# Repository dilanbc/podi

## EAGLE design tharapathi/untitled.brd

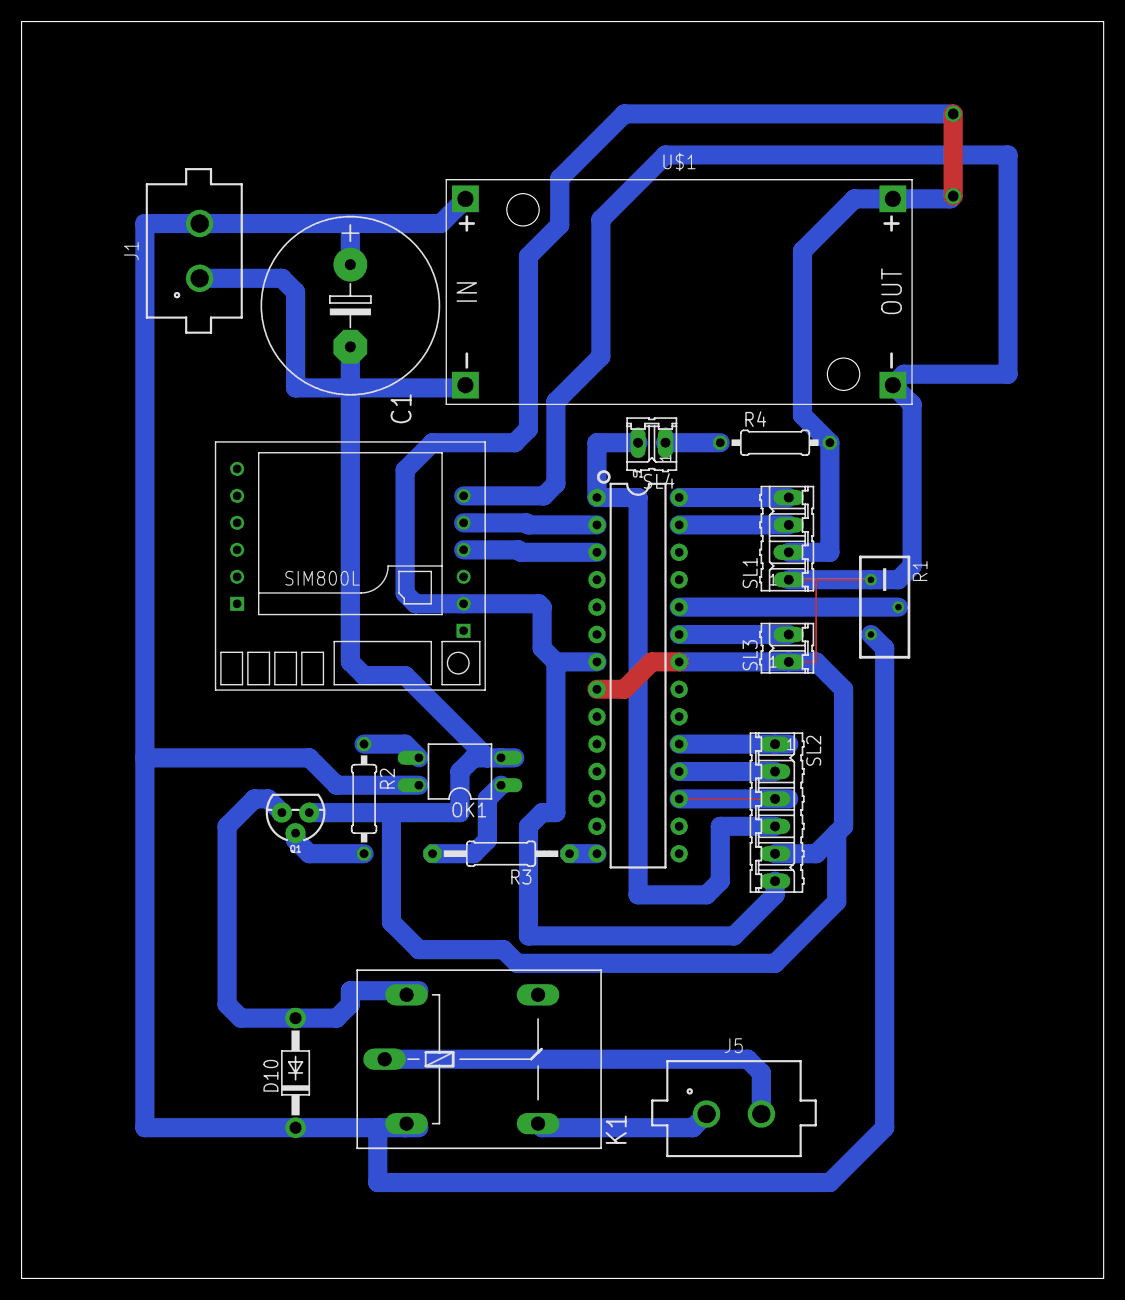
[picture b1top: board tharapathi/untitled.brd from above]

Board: 2 copper layers, 100.3 x 116.5 mm, 18 parts (0 on the bottom side), 21 nets.

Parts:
C1: E7,5-16
D10: 1N4004; DO41-10
J1, J5: 691305530002
K1: G5L; G5LE
OK1: PC817; DIL04
Q1: 200mA/40V; TO-92
R1: RTRIM3296Y
R2, R4: 0207/10
R3: 0207/12
SL1: 04P
SL2: 06P
SL3, SL4: 02P
U1: 328P; DIP28
U$1: DC-DC-STEP-DOWN-LM2596
U$2: SIM800LMODULE

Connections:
GND: C1.-, J1.1, OK1.2, Q1.1, R1.1, SL1.1, SL2.5, SL3.1, U1.8, U1.22, U$1.IN-, U$1.OUT-, U$2.GND
unnamed: OK1.1, R3.2
unnamed: R1.2, U1.24
unnamed: SL2.1, U1.19
unnamed: SL2.2, U1.18
unnamed: SL2.3, U1.17
unnamed: SL2.4, SL4.2, U1.1
unnamed: SL3.2, U1.23
unnamed: D10.A, K1.2, Q1.3
unnamed: J5.2, K1.P
unnamed: J5.1, K1.S
unnamed: Q1.2, R2.2
unnamed: OK1.3, R2.1
unnamed: R4.1, SL4.1
PWR: C1.+, D10.C, J1.2, K1.1, OK1.4, R1.3, U$1.IN+
RL: R3.1, U1.14
RX: U1.2, U$2.TX
SCL: SL1.4, U1.28
SDA: SL1.3, U1.27
TX: U1.3, U$2.RX
VCC: R4.2, SL1.2, SL2.6, U1.7, U$1.OUT+, U$2.VCC

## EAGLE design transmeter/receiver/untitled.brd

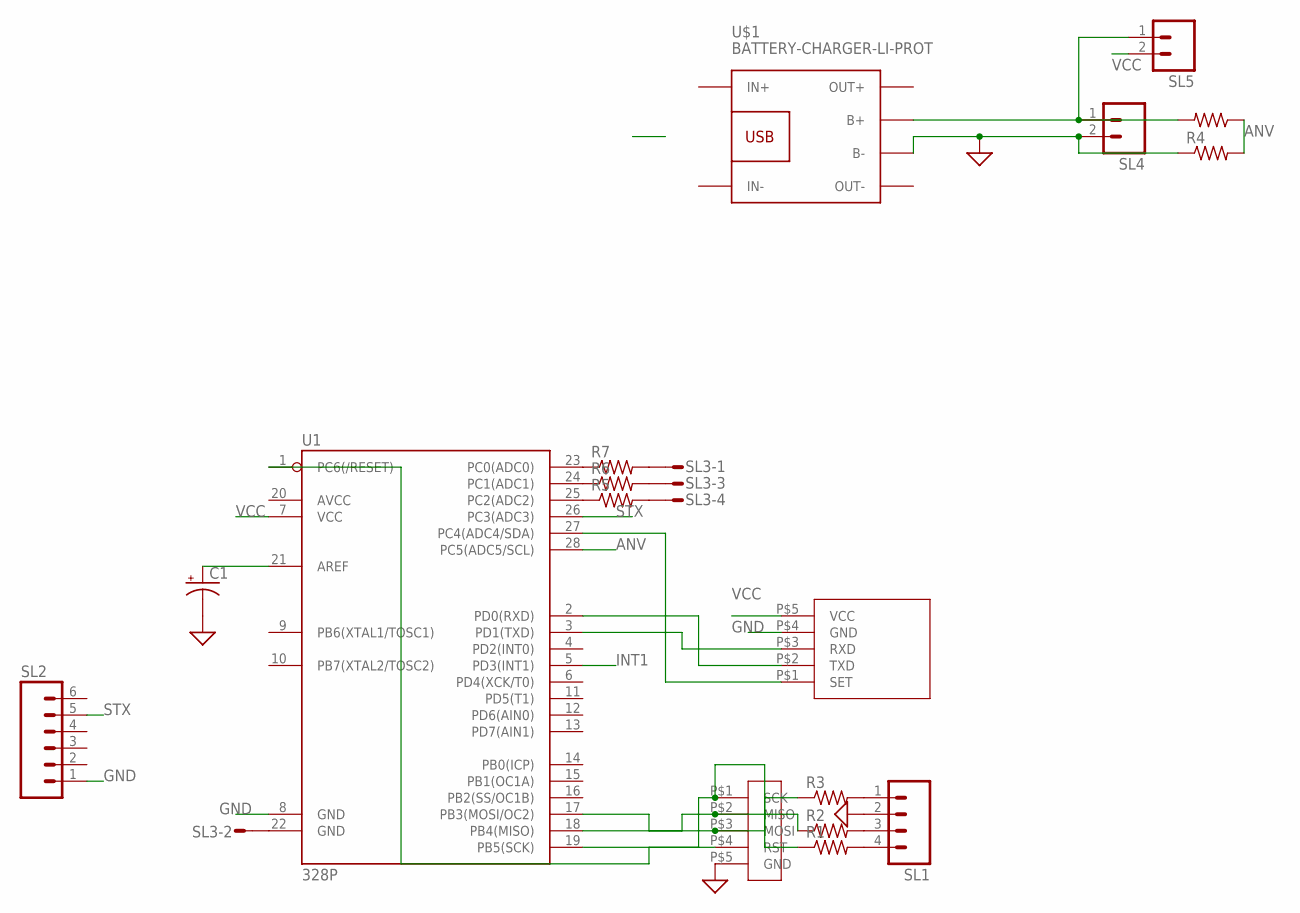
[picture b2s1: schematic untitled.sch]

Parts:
C1: CAPACITOR-PE2.5-5; E2,5-5
R1, R2, R5, R6: R-US_0204/2V; 0204V
R3: R-US_0207/7; 0207/7
R4, R8: R-US_0617/17; 0617/17
R7: R-US_0207/5V; 0207/5V
SL1: M04; 04P
SL2: M06; 06P
SL3: M04S; 04P
SL4, SL5: M02; 02P
U1: 328P; DIP28
U$1: BATTERY-CHARGER-LI-PROT
U$2: MYISP
U$3: HC12

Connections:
ANV: R4.2, R8.1, U1.28 (PC5(ADC5/SCL))
GND: C1.-, R4.1, SL1.2, SL2.1, SL4.2, U1.8 (GND), U$1.B-, U$2.P$5 (GND), U$3.P$4 (GND)
INT1: U1.5 (PD3(INT1))
unnamed: C1.+, U1.21 (AREF)
unnamed: R1.2, SL1.4
unnamed: R1.1, U1.19 (PB5(SCK)), U$2.P$1 (SCK)
unnamed: R2.1, U1.18 (PB4(MISO)), U$2.P$2 (MISO)
unnamed: R3.1, U1.17 (PB3(MOSI/OC2)), U$2.P$3 (MOSI)
unnamed: U1.1 (PC6(/RESET)), U$2.P$4 (RST)
unnamed: R2.2, SL1.3
unnamed: R3.2, SL1.1
unnamed: U1.27 (PC4(ADC4/SDA)), U$3.P$1 (SET)
unnamed: U1.2 (PD0(RXD)), U$3.P$2 (TXD)
unnamed: U1.3 (PD1(TXD)), U$3.P$3 (RXD)
unnamed: SL3.2, U1.22 (GND)
unnamed: R5.1, U1.25 (PC2(ADC2))
unnamed: R5.2, SL3.4
unnamed: R6.1, U1.24 (PC1(ADC1))
unnamed: R6.2, SL3.3
unnamed: R7.1, U1.23 (PC0(ADC0))
unnamed: R7.2, SL3.1
unnamed: R8.2, SL4.1, SL5.1, U$1.B+
STX: SL2.5, U1.26 (PC3(ADC3))
VCC: SL5.2, U1.7 (VCC), U$3.P$5 (VCC)

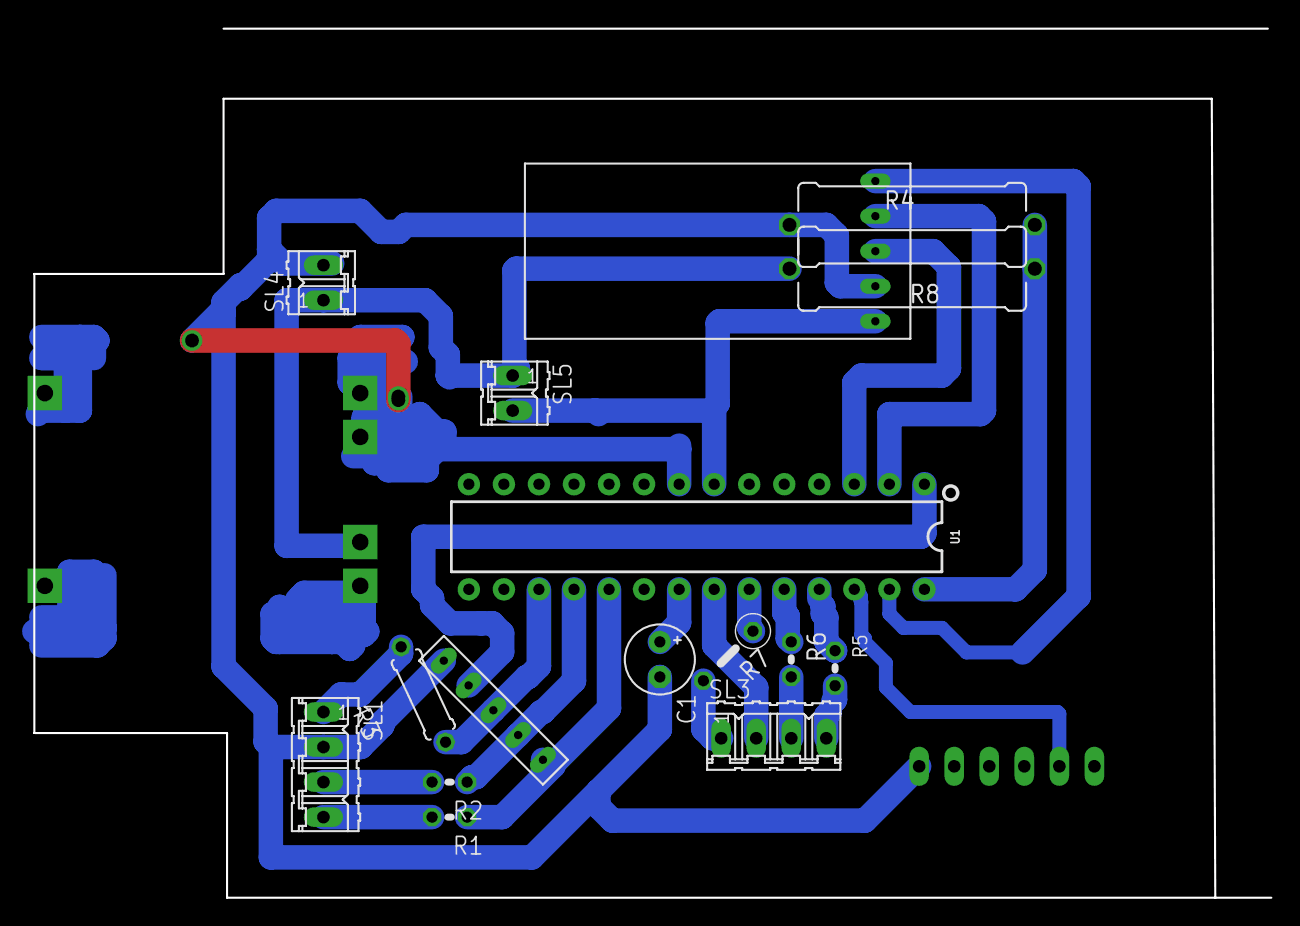
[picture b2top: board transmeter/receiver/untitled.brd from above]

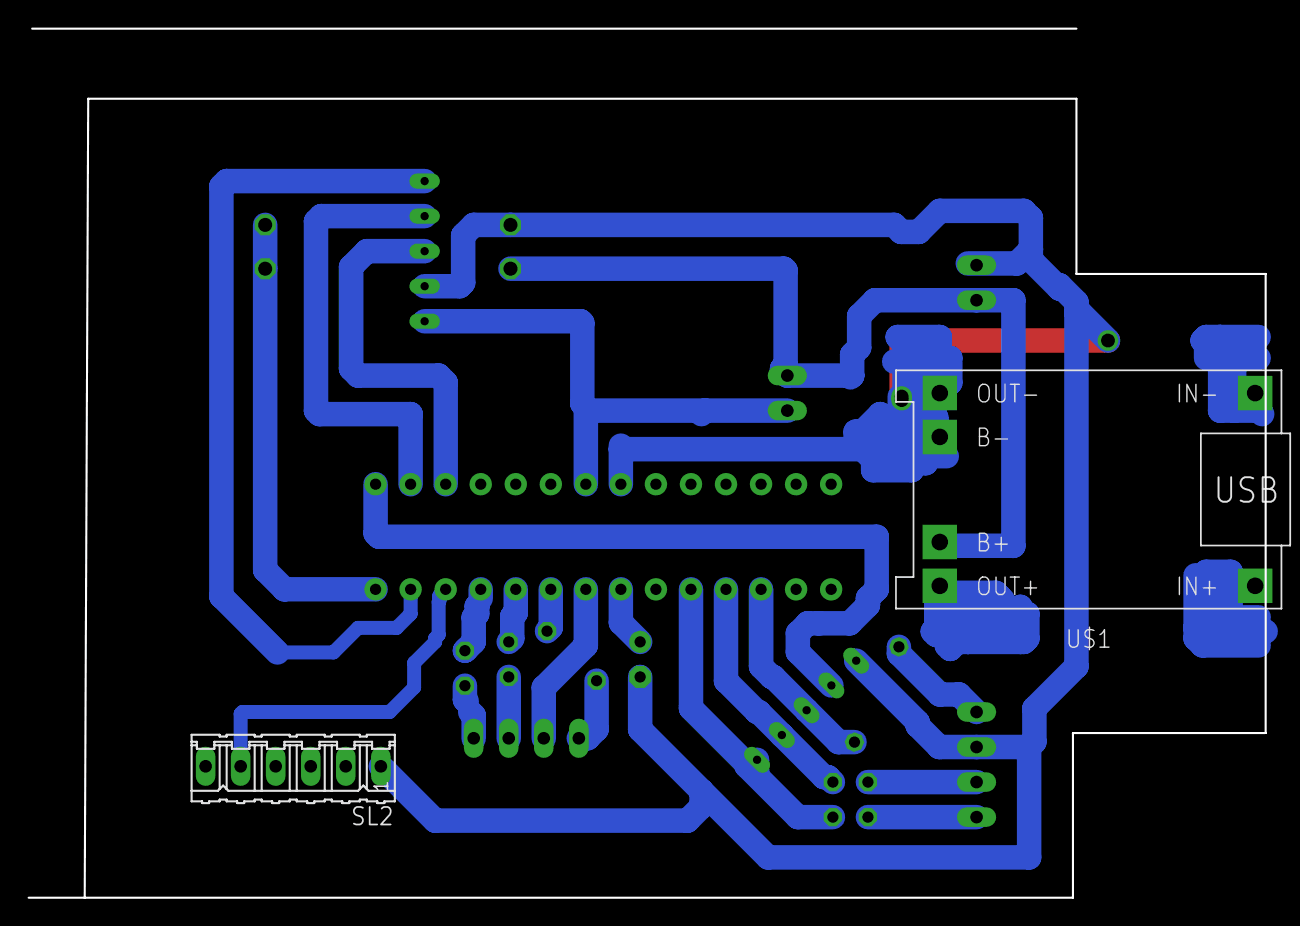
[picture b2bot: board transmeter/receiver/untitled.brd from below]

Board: 2 copper layers, 89.7 x 63.0 mm, 18 parts (2 on the bottom side), 23 nets.

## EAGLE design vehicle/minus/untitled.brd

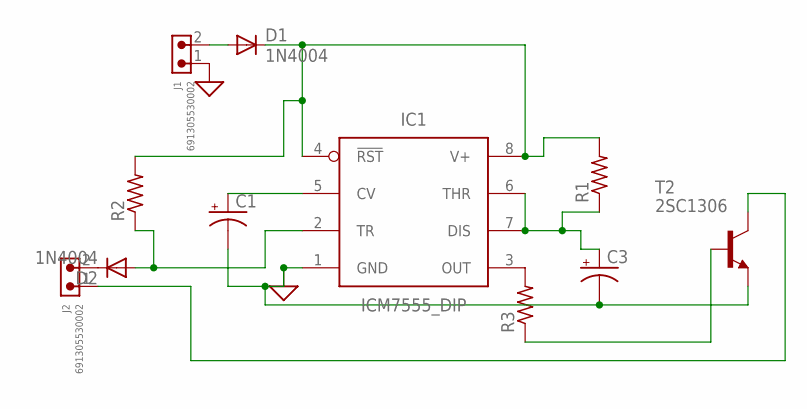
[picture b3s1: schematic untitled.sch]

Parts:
C1, C3: CAPACITOR-PE2.5-5; E2,5-5
D1, D2: 1N4004; DO41-10
IC1: ICM7555_DIP; DIP826W53P254L959H508Q8B
J1, J2: 691305530002
R1, R2: R-US_0207/7; 0207/7
R3: R-US_0207/12; 0207/12
T2: 2SC1306; TO220BV

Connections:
GND: C1.-, C3.-, IC1.1 (GND), J1.1, T2.3 (E)
unnamed: D1.A, J1.2
unnamed: D1.C, IC1.4 (!RST), IC1.8 (V+), R1.2, R2.2
unnamed: C1.+, IC1.5 (CV)
unnamed: D2.C, J2.2
unnamed: C3.+, IC1.6 (THR), IC1.7 (DIS), R1.1
unnamed: J2.1, T2.2 (C)
unnamed: D2.A, IC1.2 (TR), R2.1
unnamed: IC1.3 (OUT), R3.2
unnamed: R3.1, T2.1 (B)

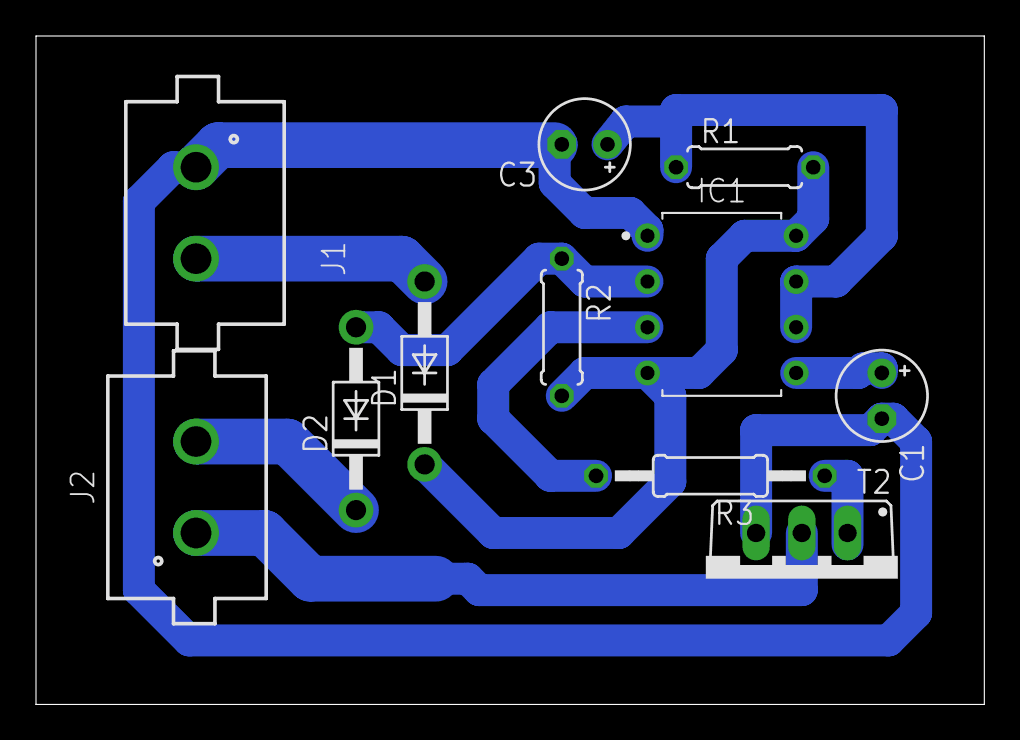
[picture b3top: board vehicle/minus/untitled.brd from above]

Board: 2 copper layers, 52.7 x 37.1 mm, 11 parts (0 on the bottom side), 10 nets.

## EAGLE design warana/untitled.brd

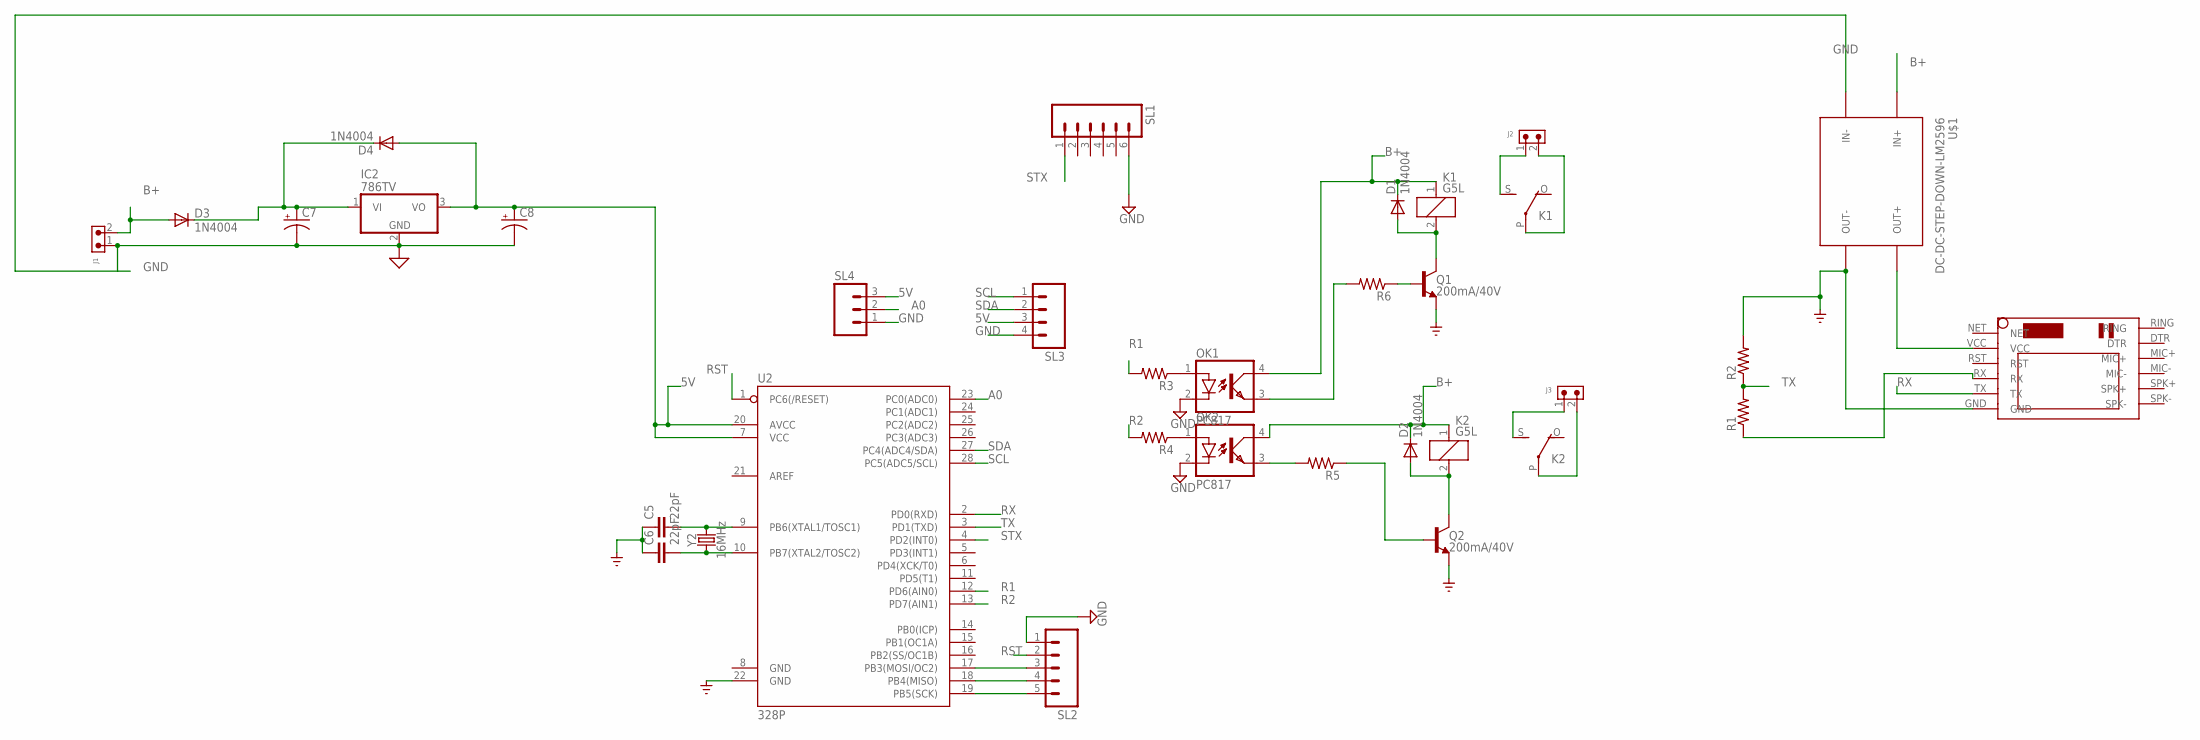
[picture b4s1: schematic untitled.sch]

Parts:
C5, C6: 22pF; CAP-PTH-2.54
C7: CAPACITOR-PE5-10.5; E5-10,5
C8: CAPACITOR-PE5-6; E5-6
D1, D2, D3, D4: 1N4004; DO41-10
IC2: 786TV; TO220V
J1, J2, J3: 691305530002
K1, K2: G5L; G5LE
OK1, OK2: PC817; DIL04
Q1, Q2: 200mA/40V; TO-92
R1, R2, R3, R4, R5, R6: R-US_0207/9; 0207/9
SL1: M06; 06P
SL2: M05; 05P
SL3: M04; 04P
SL4: M03; 03P
U2: 328P; DIP28
U$1: DC-DC-STEP-DOWN-LM2596
U$2: SIM800LMODULE
Y2: 16MHz; HC49US

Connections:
5V: C8.+, D4.A, IC2.3 (VO), SL3.3, SL4.3, U2.7 (VCC), U2.20 (AVCC)
A0: SL4.2, U2.23 (PC0(ADC0))
B+: D1.C, D2.C, D3.A, J1.2, K1.1, K2.1, OK1.4 (COL), OK2.4 (COL), U$1.IN+
GND: C5.1, C6.1, C7.-, C8.-, IC2.2 (GND), J1.1, OK1.2 (C), OK2.2 (C), Q1.1 (E), Q2.1 (E), R2.2, SL1.6, SL2.1, SL3.4, SL4.1, U2.22 (GND), U$1.IN-, U$1.OUT-, U$2.GND
unnamed: U$1.OUT+, U$2.VCC
unnamed: R1.1, U$2.RX
unnamed: OK1.1 (A), R3.1
unnamed: OK2.1 (A), R4.1
unnamed: SL2.5, U2.19 (PB5(SCK))
unnamed: SL2.4, U2.18 (PB4(MISO))
unnamed: SL2.3, U2.17 (PB3(MOSI/OC2))
unnamed: J3.1, K2.S
unnamed: J3.2, K2.P
unnamed: J2.1, K1.S
unnamed: C7.+, D3.C, D4.C, IC2.1 (VI)
unnamed: C6.2, U2.10 (PB7(XTAL2/TOSC2)), Y2.1
unnamed: C5.2, U2.9 (PB6(XTAL1/TOSC1)), Y2.2
unnamed: J2.2, K1.P
unnamed: D1.A, K1.2, Q1.3 (C)
unnamed: D2.A, K2.2, Q2.3 (C)
unnamed: OK1.3 (EMIT), R6.2
unnamed: Q1.2 (B), R6.1
unnamed: OK2.3 (EMIT), R5.2
unnamed: Q2.2 (B), R5.1
R1: R3.2, U2.12 (PD6(AIN0))
R2: R4.2, U2.13 (PD7(AIN1))
RST: SL2.2, U2.1 (PC6(/RESET))
RX: U2.2 (PD0(RXD)), U$2.TX
SCL: SL3.1, U2.28 (PC5(ADC5/SCL))
SDA: SL3.2, U2.27 (PC4(ADC4/SDA))
STX: SL1.1, U2.4 (PD2(INT0))
TX: R1.2, R2.1, U2.3 (PD1(TXD))

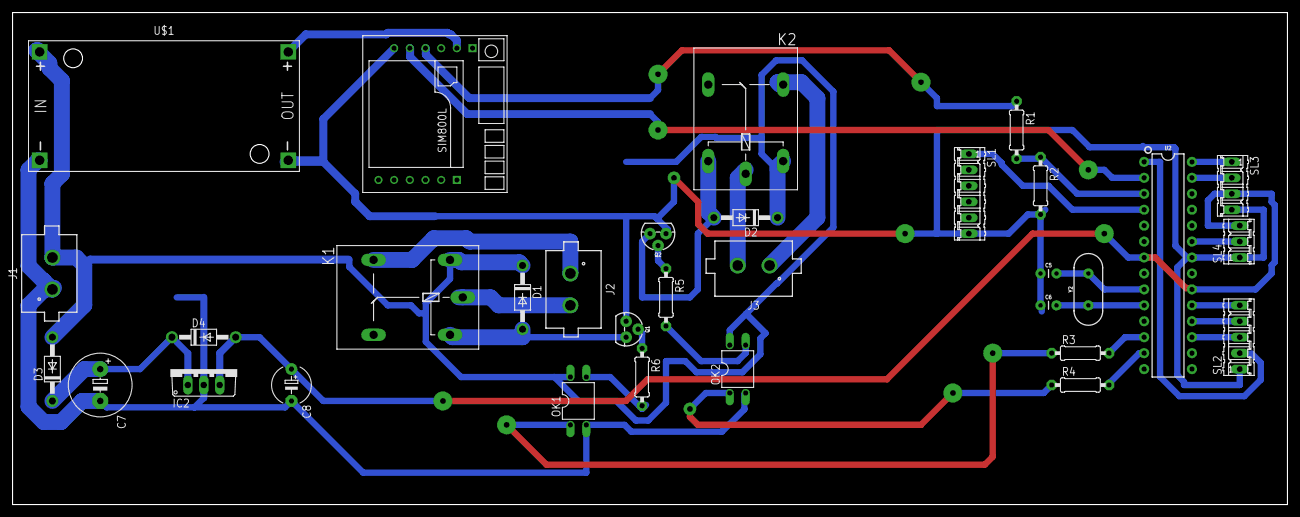
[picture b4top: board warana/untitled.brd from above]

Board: 2 copper layers, 203.2 x 78.4 mm, 32 parts (0 on the bottom side), 32 nets.

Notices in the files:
parts and their libraries:
SparkFun-IC-Microcontroller: Licensing: Creative Commons ShareAlike 4.0 International - https://creativecommons.org/licenses/by-sa/4.0
Wurth_Connectors_WR-TBL Pluggable Connec: Copyright: Würth Elektronik
